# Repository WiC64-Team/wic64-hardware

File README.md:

<p xmlns:cc="http://creativecommons.org/ns#" xmlns:dct="http://purl.org/dc/terms/"><a property="dct:title" rel="cc:attributionURL" href="https://wic64.com">WiC64</a> by <a rel="cc:attributionURL dct:creator" property="cc:attributionName" href="https://wic64.com">GMP</a> is licensed under <a href="https://creativecommons.org/licenses/by/4.0/?ref=chooser-v1" target="_blank" rel="license noopener noreferrer" style="display:inline-block;">CC BY 4.0</a></p>

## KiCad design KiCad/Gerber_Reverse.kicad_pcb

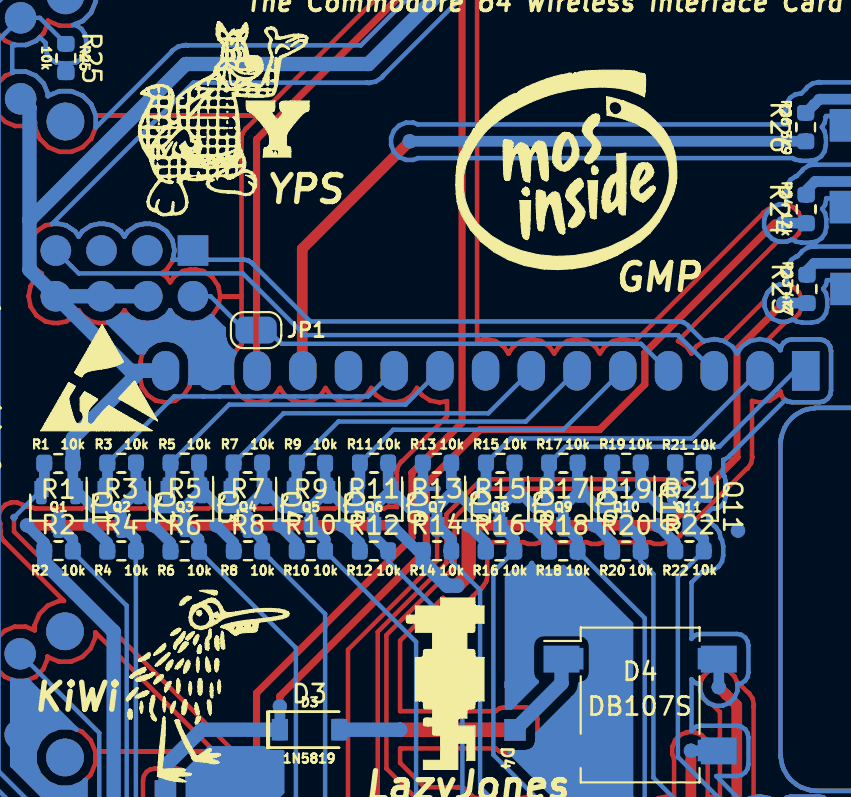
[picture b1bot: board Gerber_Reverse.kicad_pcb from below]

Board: 2 copper layers, 39 parts (39 on the bottom side), 25 nets.

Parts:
D3: 1N5819; D_SOD-123
D4: MDB10S; DIOB_DB107S
Q1, Q2, Q3, Q4, Q5, Q6, Q7, Q8, Q9, Q10, Q11: BSS138; SOT-23
R1, R2, R3, R4, R5, R6, R7, R8, R9, R10, R11, R12, R13, R14, R15, R16, R17, R18, R19, R20, R21, R22: R; R_0603_1608Metric
R23: 4k7; R_0603_1608Metric
R24: 12k; R_0603_1608Metric
R25, R26: 10k; R_0603_1608Metric

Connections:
+3.3V: Q1.1 (G), Q2.1 (G), Q3.1 (G), Q4.1 (G), Q5.1 (G), Q6.1 (G), Q7.1 (G), Q8.1 (G), Q9.1 (G), Q10.1 (G), Q11.1 (G), R1.1, R3.1, R5.1, R7.1, R9.1, R11.1, R13.1, R15.1, R17.1, R19.1, R21.1
+5V: R2.1, R4.1, R6.1, R8.1, R10.1, R12.1, R14.1, R16.1, R18.1, R20.1, R22.1, R23.1
FLAG2: Q1.3 (D), R2.2
IO14: Q7.2 (S), R13.2
IO16: Q2.2 (S), R3.2
IO17: Q3.2 (S), R5.2
IO18: Q4.2 (S), R7.2
IO19: Q5.2 (S), R9.2
IO21: Q6.2 (S), R11.2
IO22: Q8.2 (S), R15.2
IO23: Q9.2 (S), R17.2
IO25: Q10.2 (S), R19.2
IO26: Q1.2 (S), R1.2
IO27: Q11.2 (S), R21.2
PA2: Q11.3 (D), R22.2
PB0: Q2.3 (D), R4.2
PB1: Q3.3 (D), R6.2
PB2: Q4.3 (D), R8.2
PB3: Q5.3 (D), R10.2
PB4: Q6.3 (D), R12.2
PB5: Q8.3 (D), R16.2
PB6: Q9.3 (D), R18.2
PB7: Q10.3 (D), R20.2
PC2: Q7.3 (D), R14.2
VCC: D3.1 (K), R24.1

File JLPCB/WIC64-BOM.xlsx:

Comment | Designator | Footprint | JLCPCB Part #（optional）
BSS138 | Q1, Q2, Q3, Q4, Q5, Q6, Q7, Q8, Q9, Q10, Q11 | SOT-23 | C427380
DB107S | D4 | DBS | C5345971
1N5819W | D3 | SOD-123 | C5451628
100mW ±100ppm/℃ ±5% 10kΩ 0603 Chip Resistor - Surface Mount | R1, R2, R3, R4, R5, R6, R7, R8, R9, R10, R11, R12, R13, R14, R15, R16, R17, R18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 | 0603 | C3152154
100mW ±100ppm/℃ ±1% 4.7kΩ 0603 Chip Resistor - Surface Moun | R23 | 0603 | C3017722
100mW Thick Film Resistors ±100ppm/℃ ±5% 12kΩ 0603 Chip Resistor - Surface Moun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 | R24 | 0603 | C25577
100mW Thick Film Resistors ±1% 3.9kΩ 0603 Chip Resistor - Surface Mount ROHS | R26 | 0603 | C285216

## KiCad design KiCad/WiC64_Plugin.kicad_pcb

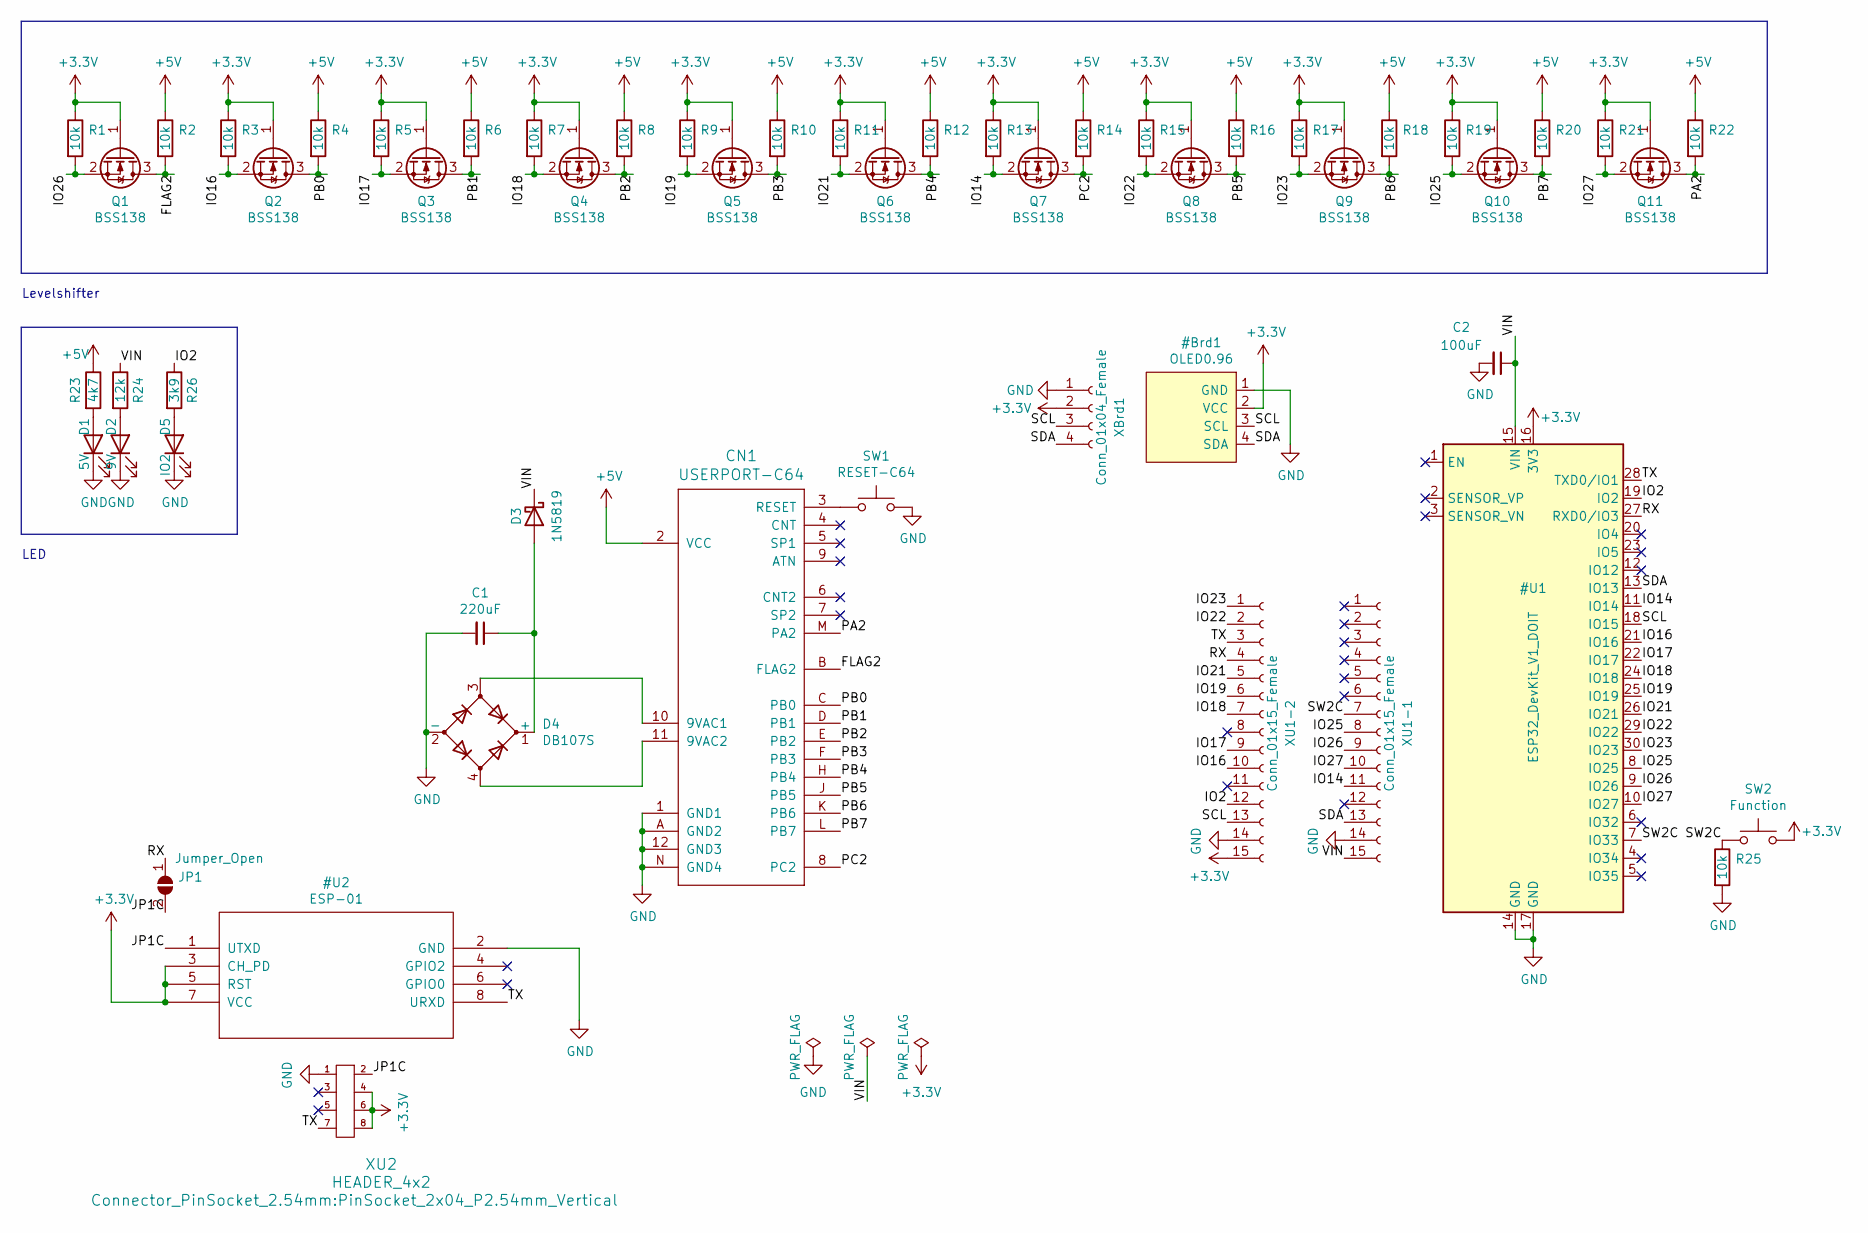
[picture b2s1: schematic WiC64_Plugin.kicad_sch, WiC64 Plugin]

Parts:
C1: 220uF; CP_6.3x11mm_hor; LCSC C269997
C2: 100uF; CP_6.3x11mm_hor; LCSC C106598
CN1: USERPORT-C64; UPS24CONN
D1: 5V; LED_D3.0mm; LCSC C568936
D2: 9V; LED_D3.0mm; LCSC C568937
D3: 1N5819; D_SOD-123; LCSC C402219
D4: DB107S; Diode_Bridge_Diotec_SO-DIL-Slim; LCSC C190797
D5: IO2; LED_D3.0mm; LCSC C331056
JP1: Jumper_Open; SolderJumper-2_P1.3mm_Open_RoundedPad1.0x1.5mm
Q1, Q2, Q3, Q4, Q5, Q6, Q7, Q8, Q9, Q10, Q11: BSS138; SOT-23; LCSC C112239
R1, R2, R3, R4, R5, R6, R7, R8, R9, R10, R11, R12, R13, R14, R15, R16, R17, R18, R19, R20, R21, R22, R25: 10k; R_0603_1608Metric; LCSC C25804
R23: 4k7; R_0603_1608Metric; LCSC C23162
R24: 12k; R_0603_1608Metric; LCSC C22790
R26: 3k9; R_0603_1608Metric; LCSC C23018
SW1: RESET-C64; SW_Tactile_SPST_Angled_PTS645Vx58-2LFS; LCSC C406160
SW2: Function; SW_Tactile_SPST_Angled_PTS645Vx58-2LFS; LCSC C406160
XBrd1: Conn_01x04_Female; PinSocket_1x04_P2.54mm_Vertical
XU1-1, XU1-2: Conn_01x15_Female; pin_socket_15
XU2: HEADER_4x2; PinSocket_2x04_P2.54mm_Vertical

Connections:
+5V: CN1.2 (VCC), R2.1, R4.1, R6.1, R8.1, R10.1, R12.1, R14.1, R16.1, R18.1, R20.1, R22.1, R23.1
/FLAG2: CN1.B (FLAG2), Q1.3 (D), R2.2
/PA2: CN1.M (PA2), Q11.3 (D), R22.2
/PB0: CN1.C (PB0), Q2.3 (D), R4.2
/PB1: CN1.D (PB1), Q3.3 (D), R6.2
/PB2: CN1.E (PB2), Q4.3 (D), R8.2
/PB3: CN1.F (PB3), Q5.3 (D), R10.2
/PB4: CN1.H (PB4), Q6.3 (D), R12.2
/PB5: CN1.J (PB5), Q8.3 (D), R16.2
/PB6: CN1.K (PB6), Q9.3 (D), R18.2
/PB7: CN1.L (PB7), Q10.3 (D), R20.2
/PC2: CN1.8 (PC2), Q7.3 (D), R14.2
unnamed: CN1.10 (9VAC1), D4.3
unnamed: CN1.11 (9VAC2), D4.4
unnamed: CN1.3 (RESET), SW1.1
unnamed: D1.2 (A), R23.2
unnamed: D2.2 (A), R24.2
unnamed: C1.1, D3.2 (A), D4.1 (+)
unnamed: D5.2 (A), R26.2

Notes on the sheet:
Levelshifter
LED

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
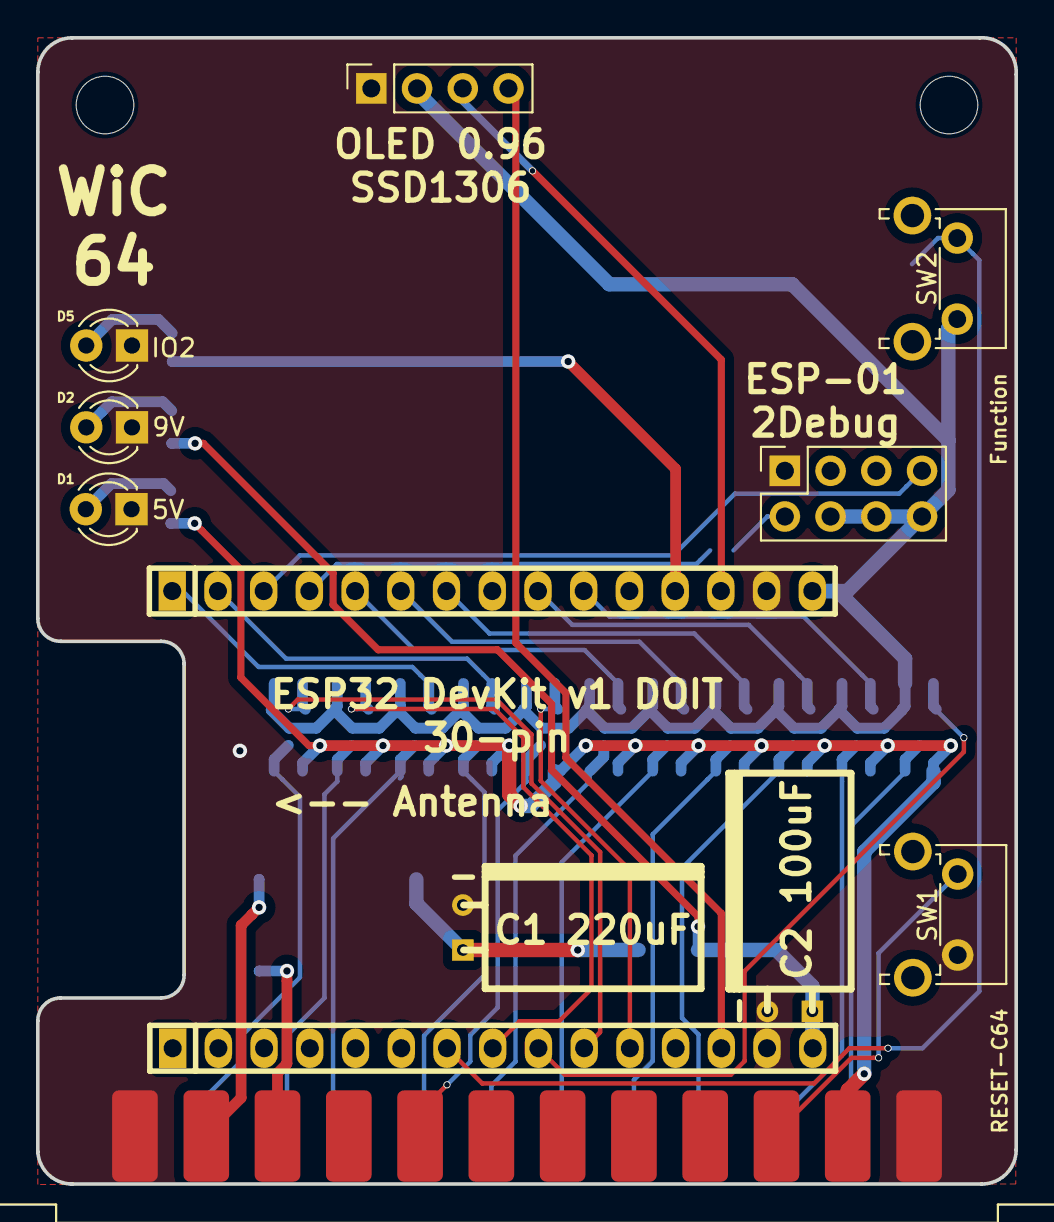
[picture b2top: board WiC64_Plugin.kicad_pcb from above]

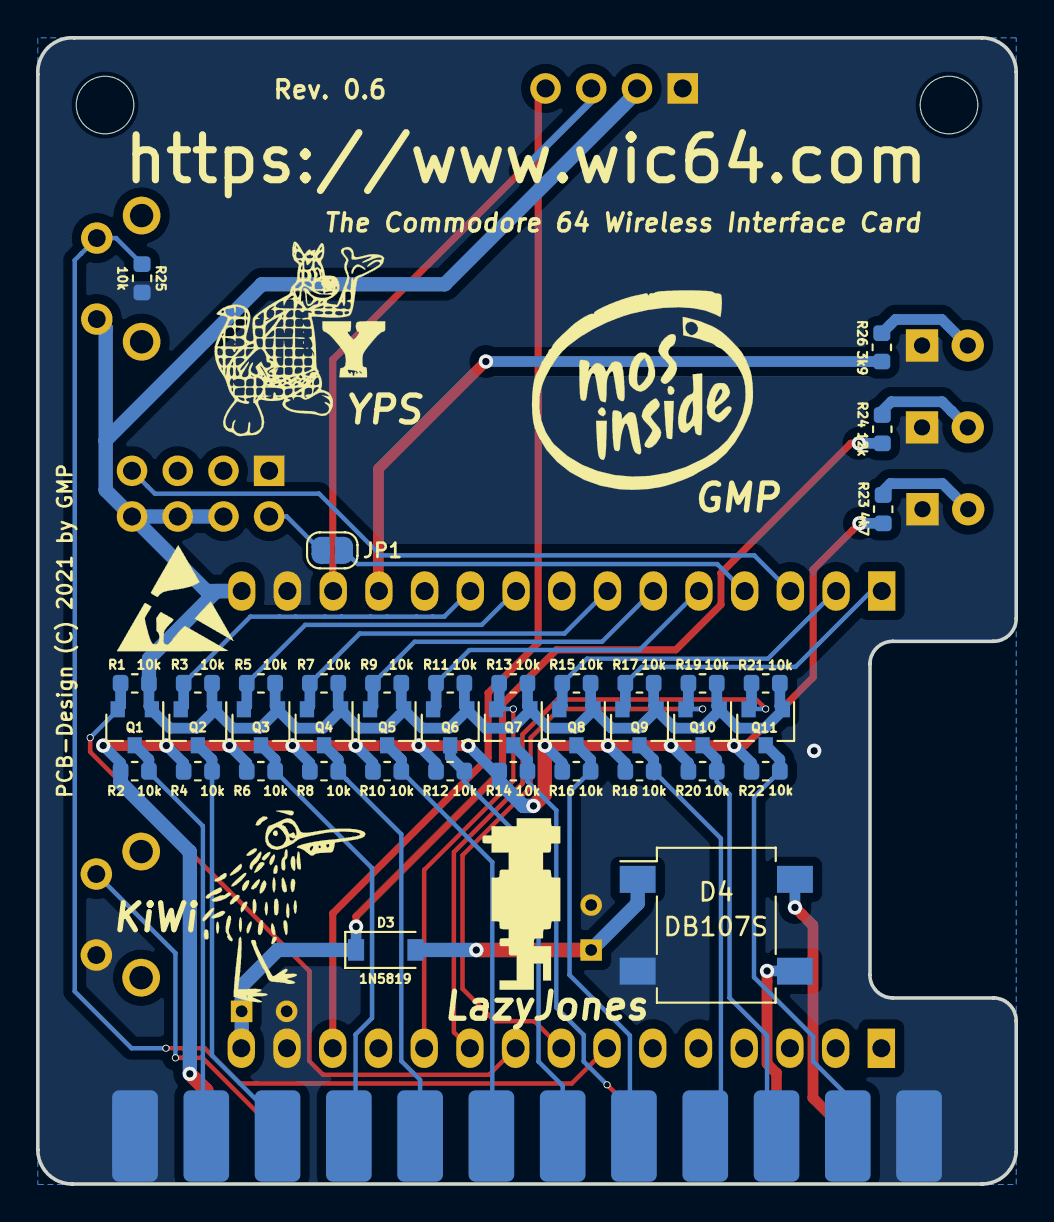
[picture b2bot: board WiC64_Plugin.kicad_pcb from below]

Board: 2 copper layers, 54.4 x 63.7 mm, 52 parts (40 on the bottom side), 40 nets.

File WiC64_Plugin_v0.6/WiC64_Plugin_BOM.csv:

ID,Designator,Package,Quantity,Designation,
2,"Q11,Q3,Q4,Q1,Q5,Q2,Q6,Q9,Q7,Q8,Q10",SOT-23,11,BSS138,BSS138
3,D3,D_SOD-123,1,1N5819,1N5819/B5819W
4,D2,LED_D3.0mm yellow,1,9V,HL-304S33YD
5,D1,LED_D3.0mm red,1,5V,HL-304S9AD
7,C1,CP_6.3x11mm_hor,1,220uF/25V,LKMC1101E221MF
8,C2,CP_6.3x11mm_hor,1,100uF/25V,ERM1EM101E11OT
9,SW1,SW_Tactile_SPST_Angled_9mm_switch_height,1,RESET-C64,TC-1102N-C-DS-B
10,D4,Diode_Bridge_Diotec_SO-DIL-Slim,1,DB107S,DB107S
11,"R1,R2,R3,R4,R5,R6,R7,R8,R9,R10,R11,R12,R13,R14,R15,R16,R17,R18,R19,R20,R21,R22,R25",R_0603_1608Metric,23,10k,0603WAF1002T5E
12,R23,R_0603_1608Metric,1,4k7,0603WAF4701T5E
13,R24,R_0603_1608Metric,1,12k,0603WAF1202T5E
14,SW2,SW_Tactile_SPST_Angled_9mm_switch_height,1,Function,TC-1102N-C-DS-B
15,D5,LED_D3.0mm green,1,IO2,TJ-L3FYTGCGMCGLFLC2G-A5
16,R26,R_0603_1608Metric,1,3k9,0603WAF3901T5E
17,XBrd1,PinSocket_1x04_P2.54mm_Vertical,1,Conn_01x04_Female,"female header 1*4pin 2.54mm, height 8.51mm"
18,XU2,PinSocket_2x04_P2.54mm_Vertical,1,Conn_02x04_Female,"female header 2*4pin 2.54mm,height 8.51mm "
24,"XU1-1,XU1-2",PinSocket_1x15_P2.54mm_Vertical,2,Conn_01x15_Female,"female header 1*15pin 2.54mm, height 8.51mm"

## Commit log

2023-08-30 Create test
2024-03-14 everything for a jplcb order
2024-05-17 add license

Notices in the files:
KiCad/WiC64_Plugin.kicad_pcb:
(C) 2021 by GMP
PCB-Design (C) 2021 by GMP
